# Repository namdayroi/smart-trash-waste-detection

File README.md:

# Hệ thống Phân Loại Rác Tự Động (Smart Trash Classifier System)

Dự án Đồ án tốt nghiệp nghiên cứu, thiết kế và chế tạo hệ thống phân loại rác thông minh tích hợp Thị giác máy tính (Computer Vision), Trí tuệ nhân tạo (YOLOv11m) và Internet of Things (IoT). Hệ thống được triển khai trên kiến trúc phân tán gồm 3 Node kết nối qua mạng Wi-Fi mạng cục bộ (LAN).

---

## 📂 Cấu trúc thư mục dự án (Project Directory Structure)

Dự án được tổ chức một cách khoa học và tối ưu để quản lý cả phần mềm, firmware vi điều khiển, thiết kế phần cứng PCB và tài liệu báo cáo:

```
SmartTrashClassifier/
├── README.md                           # Hướng dẫn chi tiết cài đặt và vận hành hệ thống
├── Images/                             # Tập hợp hình ảnh kết quả thực nghiệm, biểu đồ (tài liệu đồ án)
├── Documentation/                      # Báo cáo thuyết minh và tài liệu thiết kế đồ án
│   └── Graduation_Thesis.docx          # File báo cáo đồ án tốt nghiệp thuyết minh chi tiết
├── Software_PC/                        # Phần mềm xử lý trung tâm và chạy AI trên máy tính
│   ├── run_pc_app.py                   # Script ứng dụng chính (CustomTkinter GUI + YOLO Object Tracking)
│   ├── config.json                     # File cấu hình kết nối, ngưỡng tin cậy AI, danh sách class rác
│   ├── stats.db                        # Cơ sở dữ liệu SQLite lưu lịch sử phân loại rác cục bộ
│   └── system.log                      # Nhật ký (log) ghi nhận lỗi và trạng thái hệ thống
├── Firmware/                           # Chương trình nạp cho các vi điều khiển ESP32
│   ├── Camera_Node/                    # Node ESP32-S3 Cam làm nhiệm vụ truyền dòng video MJPEG
│   │   ├── Camera_Node.ino             # File chương trình chính cho module camera
│   │   ├── app_httpd.cpp               # Cấu hình Web Server truyền hình ảnh chất lượng cao
│   │   ├── camera_index.h              # File chứa mã HTML cấu hình thông số camera
│   │   ├── camera_pins.h               # Định nghĩa sơ đồ chân camera ESP32-S3 EYE
│   │   └── partitions.csv              # Phân vùng bộ nhớ flash (nới rộng phân vùng app)
│   ├── Controller_Node/                # Node ESP32 điều khiển cơ cấu phân loại (Bản nâng cao v3.0)
│   │   └── Controller_Node.ino         # Máy trạng thái điều khiển động cơ bước, servo, và cổng API
│   └── Controller_Node_Simple/         # Node ESP32 điều khiển cơ cấu (Bản cơ bản v1.0 - Dự phòng)
│       └── Controller_Node_Simple.ino  # Code điều khiển cơ bản, kết nối Wi-Fi thủ công
└── Hardware_PCB/                       # Thiết kế sơ đồ nguyên lý và layout mạch in (KiCad)
    ├── THUNGRAC_AI_CAM.kicad_pcb       # Bản vẽ thiết kế mạch in PCB 
    ├── THUNGRAC_AI_CAM.kicad_sch       # Sơ đồ nguyên lý toàn mạch
    ├── THUNGRAC_AI_CAM.kicad_pro       # Quản lý cấu hình dự án KiCad
    ├── THUNGRAC_AI_CAM.kicad_prl       # File lưu trữ cài đặt hiển thị cục bộ
    ├── THUNGRAC_AI_CAM.svg             # Sơ đồ mạch điện xuất ra định dạng ảnh vector
    ├── Library.pretty/                 # Tập hợp footprint linh kiện nội bộ của mạch
    ├── THUNGRAC_AI_CAM-backups/        # Thư mục chứa các file sao lưu tự động của dự án
    └── Libraries/                      # Thư viện mô hình 3D (STEP/WRL) của các linh kiện bên ngoài
        ├── ESP32-S3-DEVKITC-1U-N8R8/   # Thư viện footprint & 3D cho ESP32-S3 DevKit
        ├── LM2596-StepDown/            # Thư viện footprint & 3D cho mạch giảm áp LM2596
        └── TMC2209-Driver/             # Thư viện footprint & 3D cho module Driver TMC2209
```

---

## 🛠️ Sơ đồ Kiến trúc & Luồng hoạt động (System Architecture & Dataflow)

Hệ thống hoạt động theo mô hình luồng khép kín thời gian thực:
1. **Thu thập dữ liệu hình ảnh (Camera Node)**: Module ESP32-S3 Cam thu nhận hình ảnh từ camera OV2640 và truyền phát liên tục dưới dạng luồng MJPEG Stream qua giao thức HTTP ở cổng `81`.
2. **Xử lý trí tuệ nhân tạo (Central PC Node)**: 
   * Máy tính PC kết nối vào luồng stream, giải mã từng khung hình.
   * Áp dụng mô hình **YOLOv11m** được tối ưu hóa để định vị các loại rác thải.
   * Bộ theo dõi đối tượng (**Object Tracking**) gán ID duy nhất cho mỗi vật thể để tránh phát hiện lặp lại.
   * Khi xác định loại rác vượt qua ngưỡng tin cậy (Confidence Threshold), PC gửi một yêu cầu GET HTTP đến `Controller_Node` qua API: `http://<CONTROLLER_IP>/sort?class=<CLASS_ID>`.
   * Ghi nhận lịch sử phân loại vào cơ sở dữ liệu **SQLite** cục bộ và đồng bộ lên **Firebase Cloud**.
3. **Thực thi phân loại (Controller Node)**:
   * Nhận lệnh từ PC, chuyển sang trạng thái phân loại tương ứng.
   * Xoay khay động cơ bước đến vị trí thùng rác tương ứng.
   * Kích hoạt Servo mở cửa sập để giải phóng rác, sau đó đóng cửa và quay lại vị trí ban đầu.

---

## 🔌 1. Sơ đồ kết nối phần cứng và Pinout (`Controller_Node`)

Mạch PCB chính liên kết Node điều khiển với các linh kiện chấp hành. Dưới đây là bảng định nghĩa chân kết nối trên vi điều khiển **ESP32-S3**:

| Linh kiện chấp hành | Chân trên ESP32-S3 | Chức năng chi tiết |
| :--- | :---: | :--- |
| **Servo Motor** (Nắp cửa sập) | `GPIO 4` | Điều chế độ rộng xung (PWM) góc mở từ $105^\circ$ đến $170^\circ$. |
| **Driver Step TMC2209** (Step Pin) | `GPIO 5` | Tạo xung nhịp bước động cơ bước (NEMA 17). |
| **Driver Step TMC2209** (Dir Pin) | `GPIO 6` | Xác định chiều quay động cơ (Thuận/Nghịch). |
| **Driver Step TMC2209** (En Pin) | `GPIO 7` | Cho phép/Vô hiệu hóa driver động cơ (Tiết kiệm điện khi rảnh). |
| **Cảm biến Hall A3144** | `GPIO 15` | Cảm biến từ trường từ nam châm để xác định vị trí góc 0 (Homing). |
| **Đèn LED báo trạng thái** | `GPIO 2` | Nhấp nháy báo hiệu kết nối Wi-Fi hoặc trạng thái máy trạng thái. |

---

## 🧠 2. Máy trạng thái Node điều khiển (`Controller_Node`)

Node điều khiển cơ cấu phân loại được lập trình theo mô hình **Finit State Machine (FSM)** bất đồng bộ, giúp vi điều khiển vẫn xử lý Web Server mượt mà khi động cơ đang quay:

* **`STATE_IDLE`**: Trạng thái nghỉ, liên tục lắng nghe yêu cầu API `/sort` từ PC.
* **`STATE_HOMING`**: Trạng thái tìm điểm gốc. Động cơ bước quay chậm cho đến khi cảm biến Hall phát hiện nam châm tại khay mặc định (Góc 0).
* **`STATE_SORT_MOVING_TO_BIN`**: Xoay động cơ bước một góc tương ứng với nhãn rác nhận được:
  * *Class 0 (Chai nước)*: Quay về góc $0^\circ$ (Vị trí gốc).
  * *Class 1 (Lon nước ngọt)*: Quay về góc $90^\circ$.
  * *Class 2 (Thuốc lá)*: Quay về góc $180^\circ$.
  * *Class 3 (Vỏ kẹo)*: Quay về góc $270^\circ$.
* **`STATE_SORT_SERVO_OPENING`**: Kích hoạt Servo kéo cửa sập để mở khay chứa, cho rác rơi xuống thùng.
* **`STATE_SORT_SERVO_CLOSING`**: Servo quay ngược trở lại để đóng nắp cửa sập an toàn.
* **`STATE_SORT_FINISHING`**: Vô hiệu hóa lực giữ động cơ bước (Disable Stepper) để bảo vệ Driver khỏi bị nóng, đồng thời reset trạng thái về `STATE_IDLE`.

---

## 💻 3. Phần mềm điều khiển trung tâm trên PC (`Software_PC`)

### Thiết lập môi trường Python:
1. Đảm bảo máy tính của bạn đã được cài đặt Python 3.10 trở lên.
2. Di chuyển vào thư mục ứng dụng:
   ```bash
   cd Software_PC
   ```
3. Cài đặt các gói thư viện cần thiết:
   ```bash
   pip install customtkinter opencv-python Pillow requests ultralytics
   ```

### Giao thức Tự động dò tìm thiết bị (UDP Auto-Discovery):
Để thuận tiện khi sử dụng trong môi trường mạng Wi-Fi động (IP thay đổi liên tục), phần mềm PC tích hợp cơ chế tự động tìm kiếm IP của các Node ESP32:
* PC phát (Broadcast) định kỳ chuỗi gói tin `"WHO_IS_TRASH_CTRL"` qua giao thức UDP ở port `8888`.
* Các node ESP32 khi nhận được gói tin này sẽ phản hồi lại chuỗi `"I_AM_TRASH_CTRL|<IP_CỦA_ESP>"`.
* Giao diện PC sẽ tự động bắt lấy IP này và cập nhật vào chương trình chính mà không cần người dùng phải cấu hình IP tĩnh thủ công.

### Chạy ứng dụng:
```bash
python run_pc_app.py
```
* **AI Slider**: Cho phép tinh chỉnh trực tiếp ngưỡng tin cậy nhận diện trên giao diện.
* **Auto Tracking Mode**: Bật tính năng theo dõi vật thể bằng thuật toán tích hợp để tránh gửi trùng lệnh khi vật thể chưa đi qua hết tầm camera.

---

## 🔌 4. Thiết kế mạch PCB (`Hardware_PCB`)

Mạch thiết kế hoàn chỉnh trên phần mềm **KiCad** hỗ trợ nạp chương trình, lọc nhiễu cho động cơ công suất lớn và bảo vệ vi điều khiển:
* Sử dụng nguồn đầu vào 12V (Pin LiPo 3S hoặc Adapter) hạ áp qua Buck LM2596 để cấp dòng 5V ổn định cho hệ thống điều khiển.
* Tích hợp tụ điện chống sụt áp tức thời khi động cơ bước khởi động làm treo ESP32.
* **Tính di động của project**: Các liên kết mô hình 3D linh kiện đã được chuyển sang đường dẫn tương đối sử dụng biến môi trường `${KIPRJMOD}/Libraries/...` thay vì đường dẫn tuyệt đối tĩnh trên ổ đĩa. Nhờ vậy, khi bạn tải thư mục dự án này về bất kỳ máy tính nào khác và mở bằng KiCad, tất cả mô hình linh kiện 3D vẫn sẽ hiển thị chính xác và đầy đủ trong 3D Viewer mà không bị báo lỗi thiếu file 3D.

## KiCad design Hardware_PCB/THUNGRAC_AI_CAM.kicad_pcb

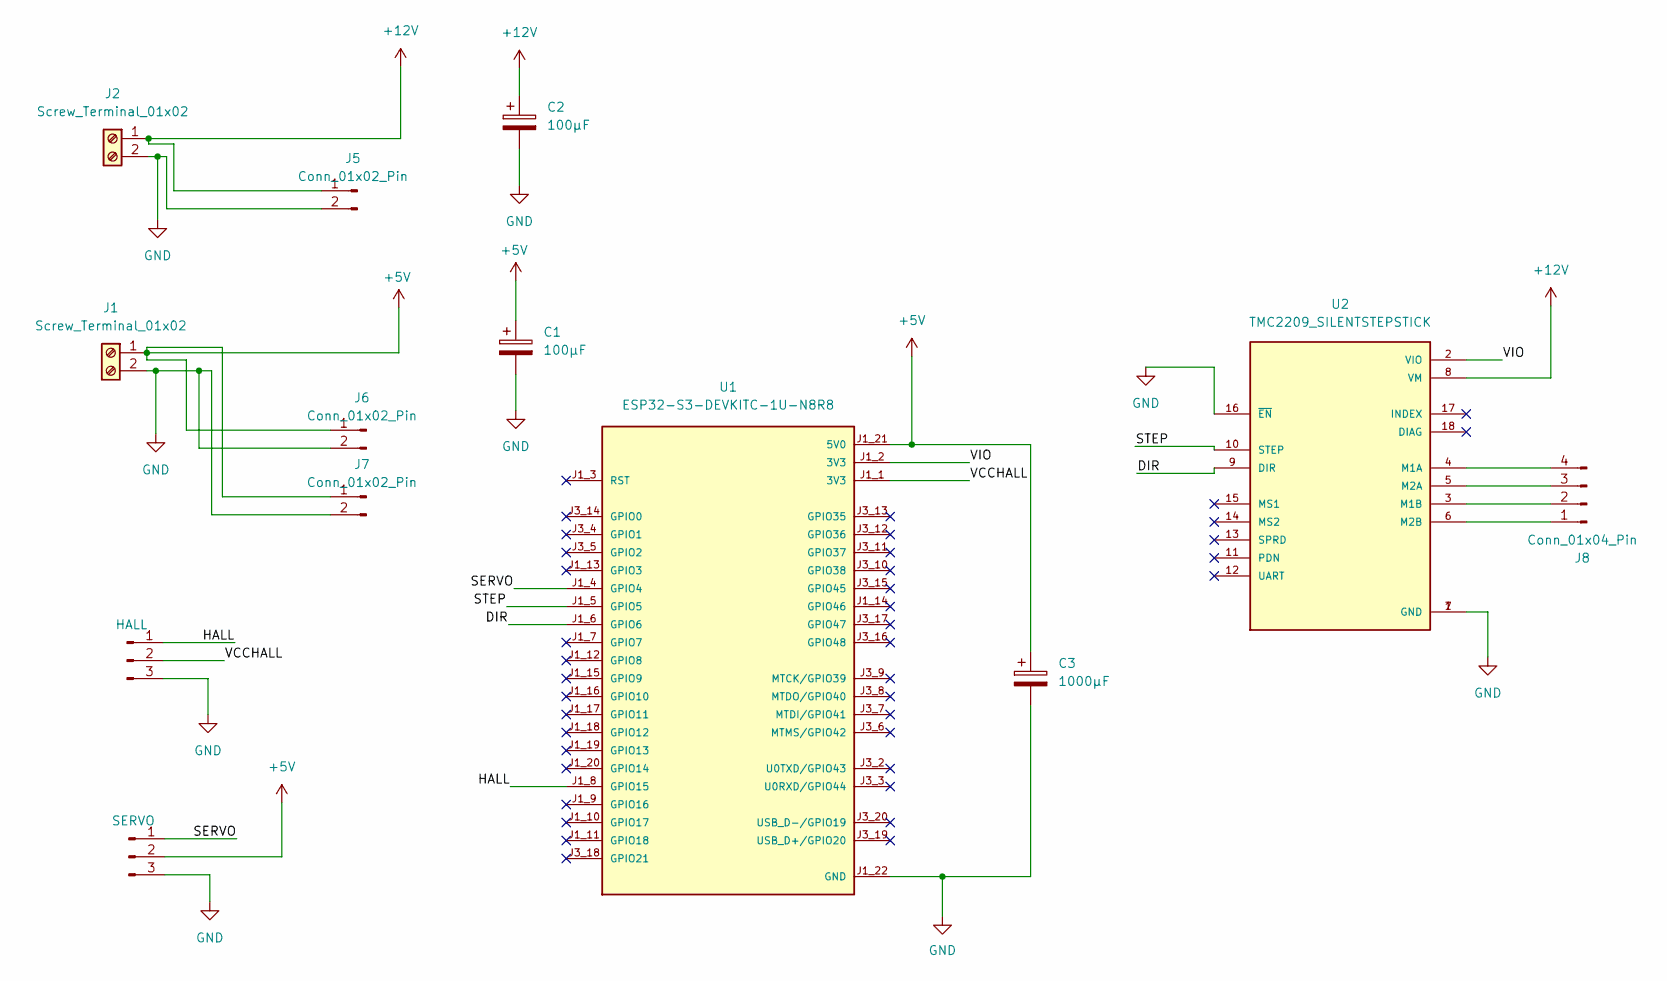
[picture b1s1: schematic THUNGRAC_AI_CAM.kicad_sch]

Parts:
C1, C2: 100µF; CP_Radial_D8.0mm_P3.50mm
C3: 1000µF; CP_Radial_D8.0mm_P3.50mm
J1, J2: Screw_Terminal_01x02; TerminalBlock_Phoenix_MKDS-1,5-2-5.08_1x02_P5.08mm_Horizont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
J3: HALL; PinHeader_1x03_P2.54mm_Vertical
J4: SERVO; PinHeader_1x03_P2.54mm_Vertical
J5, J6, J7: Conn_01x02_Pin; JST_XH_B2B-XH-A_1x02_P2.50mm_Vertical
J8: Conn_01x04_Pin; JST_XH_B4B-XH-A_1x04_P2.50mm_Vertical
U1: ESP32-S3-DEVKITC-1U-N8R8; MODULE_ESP32-S3-DEVKITC-1U-N8R8; PARTREV 1.1
U2: TMC2209_SILENTSTEPSTICK; MODULE_TMC2209_SILENTSTEPSTICK; PARTREV 1.20

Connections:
+5V: C1.1, C3.1, J1.1, J4.2, J6.1, J7.1, U1.J1_21 (5V0)
+12V: C2.1, J2.1, J5.1, U2.8 (VM)
/DIR: U1.J1_6 (GPIO6), U2.9 (DIR)
/HALL: J3.1, U1.J1_8 (GPIO15)
/SERVO: J4.1, U1.J1_4 (GPIO4)
/STEP: U1.J1_5 (GPIO5), U2.10 (STEP)
/VCCHALL: J3.2, U1.J1_1 (3V3)
/VIO: U1.J1_2 (3V3), U2.2 (VIO)
GND: C1.2, C2.2, C3.2, J1.2, J2.2, J3.3, J4.3, J5.2, J6.2, J7.2, U1.J1_22 (GND), U1.J3_1 (GND), U1.J3_21 (GND), U1.J3_22 (GND), U2.1 (GND), U2.7 (GND), U2.16 (~EN)
unnamed: J8.1, U2.6 (M2B)
unnamed: J8.2, U2.3 (M1B)
unnamed: J8.3, U2.5 (M2A)
unnamed: J8.4, U2.4 (M1A)

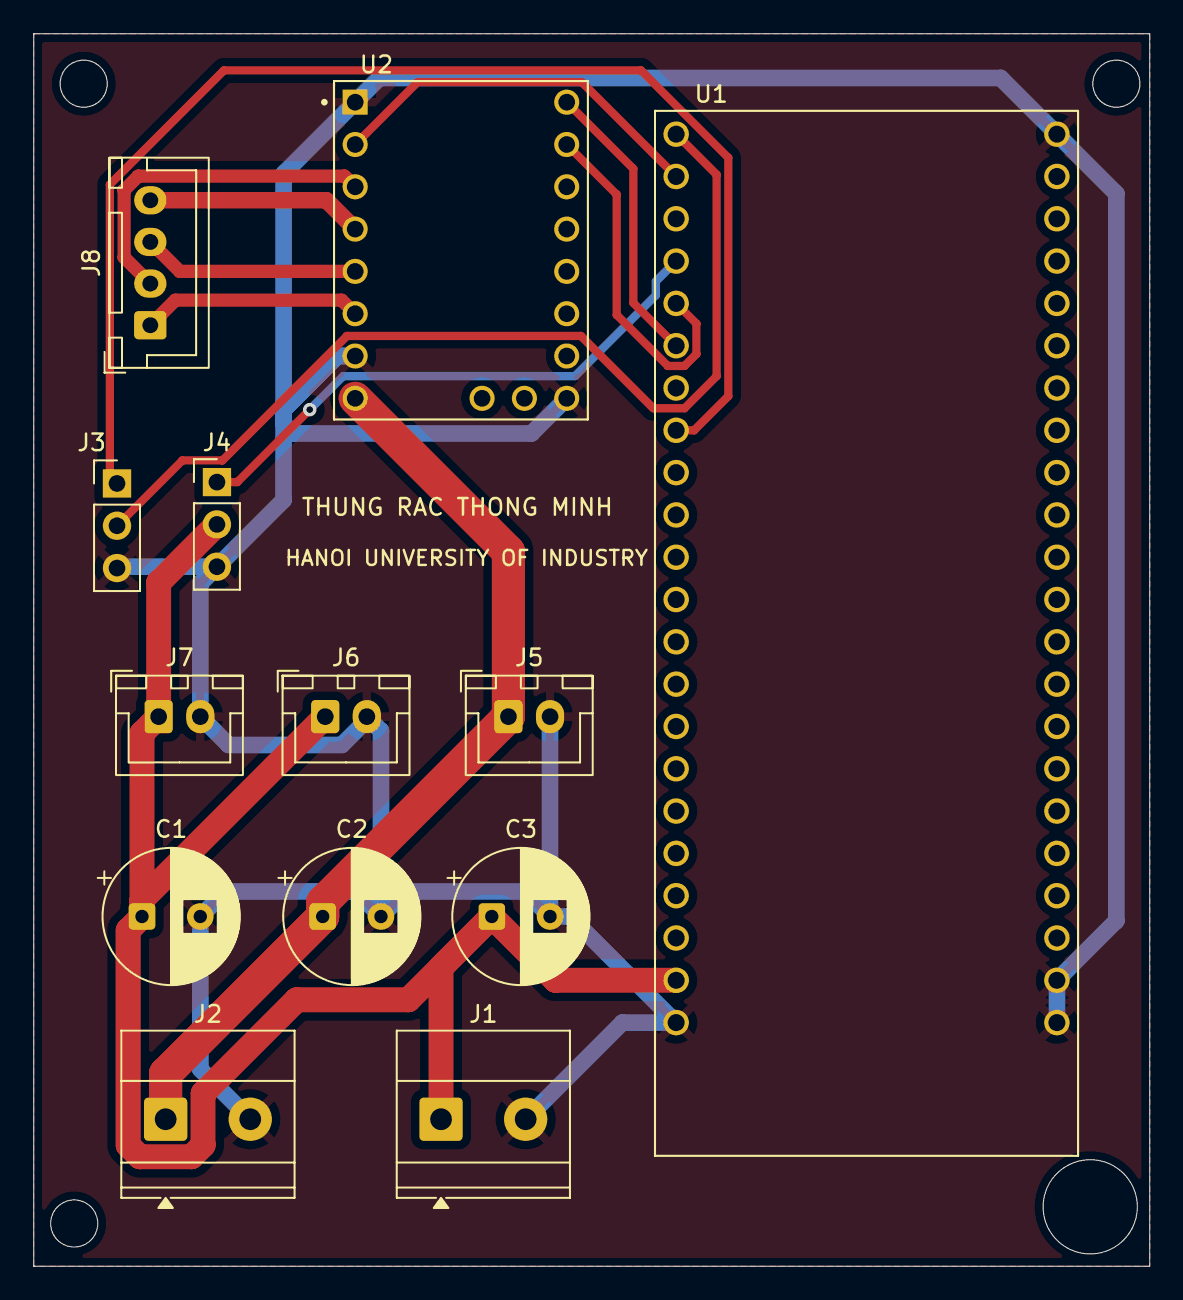
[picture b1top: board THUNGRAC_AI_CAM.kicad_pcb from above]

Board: 2 copper layers, 67.0 x 74.0 mm, 13 parts (0 on the bottom side), 13 nets.

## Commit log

2026-06-16 Initialize project structure and add README.md
2026-06-16 Remove .gitignore and include all previously ignored files
2026-06-16 Update README.md with comprehensive details and fix formatting
2026-06-16 Relocate Images directory to root and update project tree in README.md
2026-06-18 Fix logic & race bugs in PC application and Controller Node, organize deprecated folders, and add standard .gitignore to untrack temp/cache files
